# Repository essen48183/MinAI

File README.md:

# MinAI

**A single-file C++ transformer, built to be read.** Every mechanism of a modern LLM — attention, softmax, backprop, residual connections, causal masking — in ~780 lines of heavily commented code. Learns to reverse a list of 8 digits (and sort, shift, or mod-sum), demonstrating in miniature every idea that powers GPT-4.

Descends from Damien Boureille's [ATTN-11](https://github.com/dbrll/ATTN-11) (PDP-11 MACRO-11 assembly) via Dave Plummer's [2.11BSD port](https://github.com/davepl/pdpsrc/tree/main/bsd/attn). Portable C++17 — builds on macOS, Linux, and Windows.

## Why this exists

It's easy to lose the plot on what a large language model does when every explanation starts at "96 transformer blocks". This program is the plot — the irreducible version that still contains every mechanism. If you can read ~780 lines of commented C++, you understand the skeleton of every frontier model. The only difference between this and GPT-4 is quantity: more layers, more heads, more width, more data. Not one new idea.

## Quick start — two paths

### If you just want to run it (no compiler, no programming required)

Prebuilt binaries for common platforms live in [`bin/`](bin/). Grab the one for your platform and run it from a terminal:

| Platform | File | How to run |
|---|---|---|
| **macOS** (Apple Silicon or Intel) | [`bin/macos-universal/minai`](bin/macos-universal/minai) | `./minai` from a terminal |
| **Linux** (x86_64) | [`bin/linux-x86_64/minai`](bin/linux-x86_64/minai) | `./minai` from a terminal |
| **Windows** (x86_64) | [`bin/windows-x86_64/minai.exe`](bin/windows-x86_64/minai.exe) | double-click or run from `cmd`/PowerShell |

See [`bin/README.md`](bin/README.md) for details (including the macOS Gatekeeper first-run workaround). After it runs, `./minai --help` shows every flag.

### If you want to read and modify the source

**macOS / Linux** (any C++17 compiler — clang++ or g++):

```bash
make              # builds ./minai with your default C++ compiler
./minai           # trains the default config and runs a demo
./minai --help    # see all flags
```

**Windows** (and an all-platforms fallback) via CMake:

```bash
cmake -B build
cmake --build build --config Release
./build/minai --help          # macOS/Linux
./build/Release/minai.exe     # Windows MSVC
```

No external dependencies — everything needed is in the standard library. Colored sparkline output uses Unicode block characters; works in macOS Terminal, Linux terminals, and Windows Terminal (the default on Windows 11).

Abridged output:

```
MinAI — fixed example, task=reverse, seq_len=8, batch=1, blocks=1, ffn=on, causal=off
Parameters: 2240    Training steps: 800

step    loss     correct/8
-----   ------   ----------
    1   2.2802   0/8
  ...
  800   0.0078   8/8

Loss curve (800 steps, 60 columns, higher bars = higher loss):
   2.280 |▇▇▇▇▆▆▆▅▅▄▄▃▃▂▂▁▁                                        | 0.008
           step 1                                           step 800

input  : 0 1 2 3 4 5 6 7
output : 7 6 5 4 3 2 1 0
```

## Read the docs

Two companion documents live next to the source. **Read the one that matches you:**

- **[TRAINER.md](TRAINER.md)** / [TRAINER.pdf](TRAINER.pdf) — the terse operator's manual. Flag reference, task zoo, worked examples. If you already know what a transformer is and just want to drive this one, start here.

- **[ARITHMETICOFINTELLIGENCE.md](ARITHMETICOFINTELLIGENCE.md)** / [ARITHMETICOFINTELLIGENCE.pdf](ARITHMETICOFINTELLIGENCE.pdf) — *The Arithmetic of Intelligence*, a three-section textbook that builds every concept from scratch: what a model is, what attention does, why GPUs are suddenly the bottleneck of the AI industry. Section 1 (Chs 1–15) is the simple introduction, grounded in `minai.cpp` and including a hands-on walkthrough of every flag. Section 2 (Chs 16–22) grows the program into `maxai.cpp`, a toy GPT that accepts prompts, tokenizes with BPE, samples with temperature/top-k/top-p, and runs under a KV cache. Section 3 (Chs 23–28) is a career/field essay on where AI is going and why software engineering is not ending. Written for a reader who has taken some math but has never seen *why* any of it mattered; a curious adult with high-school algebra can follow it end to end.

Read either document with `minai.cpp` open alongside. The comments in the source are in the same tone and will not contradict the prose.

## Flags at a glance

```
--blocks=N      stack N transformer layers (1..96, default 1 — 96 matches GPT-3 depth)
--ffn=0|1       include the feed-forward sub-layer (default on)
--causal=0|1    causal attention mask (default off)
--layernorm=0|1 Pre-LN normalization before each sub-layer; makes deep stacks trainable
--random=0|1    train on random sequences + measure held-out accuracy (default off)
--seq_len=N     sequence length 1..32 (attention is O(N^2) in this)
--batch=B       examples averaged per step 1..128 (default 1)
--task=NAME     reverse | sort | shift | mod_sum (default reverse)
--steps=N       training iterations (default 800)
--extra_demos=0|1  run three bonus demos after training (hierarchical weight quantization,
                   speculative decoding, KV cache tiering). Each is a real LLM inference
                   technique, shown in miniature. Adds a few seconds.
```

Try `./minai --random=1 --blocks=2 --batch=16 --layernorm=1 --steps=3000` for a taste of how a real LLM trains in miniature — the model has to generalize, not memorize, and with LN + batch the grokking moment should land well before 3000 steps.

## Repo layout

```
minai.cpp            the program — 19 numbered parts, every line commented
Makefile             one-line clang++ build
TRAINER.md  .pdf     operator's manual
ARITHMETICOFINTELLIGENCE.md .pdf .docx  the book — textbook, toy-GPT growth, career essay
maxai.cpp            the Section-2 companion program (grows from minai.cpp)
README.md            this file
CLAUDE.md            instructions for the AI assistant that maintains this project
md2pdf.sh            regenerates PDFs from the .md sources
LICENSE              MIT
```

## Credit

Damien Boureille wrote the [ATTN-11](https://github.com/dbrll/ATTN-11) original in PDP-11 MACRO-11 assembly. Dave Plummer ported it to 2.11BSD `as`. This repo is the C++/Apple-Silicon rewrite with extensive annotation, a textbook companion, and runtime flags for blocks / FFN / causal / random / seq_len / batch / task. The core idea — "tiny transformer, every mechanism present, no magic" — is entirely theirs.

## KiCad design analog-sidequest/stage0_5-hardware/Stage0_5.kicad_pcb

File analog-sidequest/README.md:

# Analog MinAI — an analog compute side quest

*A parallel project that runs MinAI's math on discrete analog hardware
instead of digital CPUs/GPUs. PCB-fabbable, home-iterable in hours,
and the only reason it is tractable is that MinAI itself is small.*

---

## Why this project exists

Modern AI is a 2017 neural-network architecture running on 1990s-era
graphics hardware, burning megawatts of electricity to simulate physics
that any properly-built analog circuit does for free. Every transistor
in a GPU spends clock cycles computing `a × b + c` with floating-point
arithmetic, when Ohm's law and Kirchhoff's current law will produce the
same answer at the speed of electricity in a resistor grid.

This side project builds a physical demonstration of that argument at a
scale a single engineer can actually fabricate. It uses **MinAI's 2,240
trained weights** as its reference model, because that is a size a
handful of PCBs can hold. A GPT-3-scale analog build would need millions
of tiles and a foundry. A MinAI-scale analog build fits on a desktop.

**The book's small size is the point.** The project does not exist
despite MinAI being tiny; it exists *because* MinAI is tiny. That
smallness is a superpower here — it makes the entire "is this possible
outside a foundry?" question answerable.

---

## What a final working result looks like

A PCIe card that drops into any motherboard. On the card: a host-side
FPGA, a small onboard flash holding trained weights, and an array of
analog matmul tiles. Running MinAI's forward pass on that card should
produce the same tokens the software version produces, using
**picojoules per multiply-accumulate** (versus nanojoules for a digital
GPU) and with **no clocked computation** — the matmul settles at
analog speed.

The card is a proof of concept, not a product. What it proves is:

1. Analog compute really does match the math of a transformer.
2. The energy and speed advantages predicted by physics are measurable
   in hardware, not just simulation.
3. The build is technically within reach of a small team rather than
   an industrial fab.
4. The architecture scales — the same tile miniaturized to silicon
   with RRAM/memristor crosspoints is the known path to million-weight
   single-chip accelerators.

---

## The critical difference from prior attempts

Every commercial analog-AI attempt from 2012–2024 took the same
shortcut: *train the model on NVIDIA, deploy on our analog chip*.
That shortcut has killed every one of them commercially. The
customer math is unavoidable — if the customer already needs a
GPU for training, they just use it for inference too rather than
bring in a second vendor.

**This project treats training on the analog hardware as a
first-class, non-negotiable requirement**, addressed as Stage 0
(in simulation) and Experiment 4 of Stage 1 (on real hardware).

The core framing — different from every prior analog-AI project —
is **noise is the enemy, not representation.** Digital precision
is bounded by the number format (float32 can never exceed its
23-bit mantissa). Analog precision is bounded only by the noise
of the measurement channel, and every noise source (thermal,
flicker, shot, drift, crosstalk, EMI) has a known engineering
countermeasure. Aggressively applying those countermeasures —
precision thin-film components, autozero op-amps, delta-sigma
ADCs, 8-layer stripline PCBs, calibration reference cells — pushes
analog effective precision to **24–28 bits per operation**, which
is *better* than float32 digital on the operations where analog is
naturally exact (Kirchhoff summation, Ohm's-law multiplication,
exp/log/sqrt/tanh through diode and transistor I-V curves).

The architecture combines **three hardware precision amplifiers**
— Q8.8.8 bit-slicing (three analog cells per weight for 24-bit
nominal precision), autozero summing op-amps (20+ bit op-amp
paths), a 32-bit digital gradient accumulator, plus continuous
calibration via dedicated reference cells — with **five software
training tricks** from the 1970s–1990s analog-computing literature
— mixed-precision updates, stochastic rounding, temporal
oversampling, delta encoding, and analog physics as the native
lookup table. Together they clear the precision bar where IBM
research has demonstrated analog training of **96-layer
transformers**, not just shallow networks.

Softmax, sampling, and all nonlinearities stay analog too — the
same physics (diode `exp`, translinear divide, winner-take-all or
ramp-compare samplers) that makes matmul analog-native also makes
these operations analog-native. The host's digital footprint
reduces to: weight-load at boot, prompt-token DAC in, output-token
ID ADC out, and loop control. **One ADC-DAC round-trip per
generated token, not per layer.**

The project refuses to fabricate any hardware until a pure-
software Stage 0 simulator passes **two** gates:

- **Gate 1 (functional):** MaxAI (2 blocks) trains to recognizable
  output at simulated hardware precision.
- **Gate 2 (scaling):** MaxAI scaled to 96 blocks, same per-layer
  precision, also trains to recognizable output — proving the
  architecture scales to GPT depth in principle.

If Gate 1 fails, the project stops. If Gate 2 fails, the
GPT-depth scaling claim is retracted and the project is rescoped
as small-model-only (still valid, but a narrower pitch). Only
passing both gates clears Stage 1 to fabricate hardware.

See `ARCHITECTURE.md` for the five-trick stack and `STAGE0.md` for
the viability gate.

---

## The five stages

Each stage produces a complete, measurable artifact. Each stage's
output is the foundation for the next. Nobody has to commit to
Stage 4 before finishing Stage 1. The project has a clear inflection
at Stage 3: before it, you are proving the hardware *works*; after
it, you are proving it *matters*.

### Stage 0 — the simulator viability gate *(software only, kills the project cheaply if training doesn't work)*

- A C++ simulator of the tile architecture with Q8.8.8 bit-slicing,
  autozero op-amp paths, a 32-bit gradient accumulator,
  calibration reference cells, realistic device noise, write
  quantization, and all nine training tricks implemented.
- Runs the book's MaxAI training loop through the simulator at
  both 2-block depth (Gate 1) and 96-block depth (Gate 2).
- **Pass both gates:** architecture trains at MaxAI scale AND the
  same architecture scales to GPT-depth in principle. Proceed
  to Stage 1 with full scaling claim intact.
- **Pass Gate 1 only:** architecture trains at small scale but
  compound noise kills deeper networks. Project may still
  proceed, but the scaling claim gets retracted and the pitch
  is rescoped to "edge / small-model only."
- **Fail Gate 1:** the architecture does not train at all at this
  precision. Project stops. Zero hardware cost.
- Wall-time estimate: ~two focused weeks. Budget: $0.
- **What Stage 0 buys:** insurance against repeating Mythic's mistake
  of fabricating hardware before knowing if the architecture
  trains, *and* against the Lightmatter mistake of shipping
  hardware whose scaling ceiling wasn't known until silicon was
  in hand.

### Stage 1 — a single Q8.8.8 analog matmul tile *(validation, including one training step on real hardware)*

- Raspberry Pi Zero 2W as host.
- One small PCB holding a 16×16 analog MAC tile (256 weights).
- Performs MinAI's `Q = X @ Wq` projection entirely in analog.
- Host orchestrates: loads weights from microSD, drives inputs, reads
  outputs, compares against a NumPy/C++ reference from the book.
- Budget: **under $100 in parts**, plus your PCB fab.
- Iteration cycle: hours. Swap digipots, rework the nonlinearity, try
  different op-amps, measure on a scope.
- **What Stage 1 buys:** hardware-proven analog matmul, measurable
  against bit-exact software output. Goes no further than "the
  physics is real."

### Stage 2 — a full MinAI block in analog *(architecture proof)*

- Same Pi host, but now ~10 tiles wired together (sharing a
  backplane PCB).
- Holds MinAI's complete weight set (Q, K, V, Wout, W1, W2 of one
  block = ~2,000 weights across roughly 10 tiles).
- Pi does softmax, sampling, EOS, and tile-to-tile coordination.
  Everything else is analog.
- **What Stage 2 buys:** proof that tiling works and that a whole
  transformer block fits. The output still isn't a wow demo — it's
  MinAI still reversing digits — but the multi-tile architecture
  is proven. Everything beyond this is scaling.
- Budget: **a few hundred dollars** in parts.

### Stage 3 — MaxAI in analog *(the raised-eyebrow demo)*

- **The first demo a stranger will care about.** A Raspberry Pi
  driving a larger stack of analog tiles that holds MaxAI's weights
  (~5,000+ parameters, BPE-tokenized character vocabulary).
- User types a prompt. Pi runs the BPE tokenizer, loads token
  embeddings, streams input vectors into the analog tile array.
  Tiles compute matmuls; Pi manages the KV cache and softmax; the
  combined system generates text, token by token, at interactive
  speeds.
- Expected demo: prompt `"four score "` → analog card generates
  `"and seven years ago"`. Shown on a screen next to a laptop
  running the same model in software, producing identical tokens.
- Power budget: roughly a **watt or two** for the entire analog
  stack. The laptop next to it is pulling thirty.
- Budget: **low four figures** in parts, plus a custom backplane PCB.
- **What Stage 3 buys:** a physical artifact that demonstrates
  analog generative AI at a scale anyone can understand. This is
  the demo you show at Hackaday, Supercon, a VC meeting, a research
  group. It answers the question "could this ever matter?"

### Stage 4 — productize *or* miniaturize *(scaling path, pick one or both)*

Two branches, not necessarily exclusive. Stage 4 is the
answer to the "so what comes next?" question after the Stage-3 demo.

**Stage 4a — productize as a PCIe card.**
- Drop the Raspberry Pi. An FPGA on-card becomes the host interface.
- Card exposes a driver interface to the host PC: load weights,
  run inference, return tokens. Looks to the host like any other
  accelerator (TPU, NPU, etc.).
- Physical form: standard PCIe gen 3 ×4 slot card.
- Budget: five figures, six-month design cycle.
- **What Stage 4a buys:** a tangible product — an analog AI card
  someone can buy and plug into their desktop. Market case: edge
  inference for small language models at one-hundredth the power of
  a GPU.

**Stage 4b — miniaturize to silicon.**
- The same tile architecture, shrunk to a CMOS + RRAM process.
- Each digital potentiometer becomes a 1-transistor + 1-memristor
  crosspoint. The op-amps become integrated summing amplifiers.
  Everything else stays.
- A 256×256 tile in 22 nm fits in roughly 0.5 mm². A million-weight
  chip fits on a die smaller than a fingernail.
- Budget: $30k–$100k for a shared MPW run at a foundry that
  supports RRAM (TSMC, SMIC, IMEC).
- **What Stage 4b buys:** the definitive answer to "could this
  scale to GPT?" A single-chip version of MaxAI at a million or
  tens-of-millions of weights, at milliwatts, validates the whole
  architectural thesis. From there, larger tapeouts are engineering
  scaling, not research.

Stages 4a and 4b are not in competition. A small team that reaches
Stage 3 might do 4a first (to generate revenue) and 4b later (once
the architecture is validated enough to spend tapeout money on).

---

## The arc, in one sentence per stage

- **Stage 0:** Prove in software that the architecture can train at all, before any hardware is built.
- **Stage 1:** Prove that analog matmul AND one training step work on real hardware.
- **Stage 2:** Prove the tile architecture scales to a full transformer block, trainable.
- **Stage 3:** Prove the architecture trains and generates real text — the demo that raises eyebrows, with no GPU in the loop after initialization.
- **Stage 4:** Prove the concept scales — either to a consumer-product card or to a silicon die, both carrying training support, not inference-only.

---

## Folder contents

- `README.md` — this file.
- `ARCHITECTURE.md` — the full system architecture, piece by piece,
  with the "normal computer → analog card" mapping spelled out,
  the on-board LayerNorm stage, the stack pattern, the five
  training tricks, and the ranked constraints.
- `STAGE0.md` — **the simulator viability gate. Read first.**
  Software-only. Determines whether hardware is worth building.
- `STAGE1.md` — single-tile validation, now including the training
  experiment. Schematic, parts list, four measurement experiments.
- `STAGE2.md` — full MinAI block across multiple tiles.
- `STAGE3.md` — the MaxAI demo. Text generation from a prompt,
  on an analog-hardware stack that sits next to your laptop.
- `STAGE4.md` — the productize-or-miniaturize fork. PCIe card vs.
  silicon tapeout, both paths laid out, both carrying training
  support (not inference-only).

---

## How this relates to the book

Everything in the *Arithmetic of Intelligence* describes the
mathematics. This side quest asks whether the same mathematics can be
carried out by something other than a stack of floating-point
multipliers in a cloud-hosted GPU. The answer, apparently, is yes —
and small enough to fit on a desk.

If MinAI were larger, this project would be out of reach. It is not.

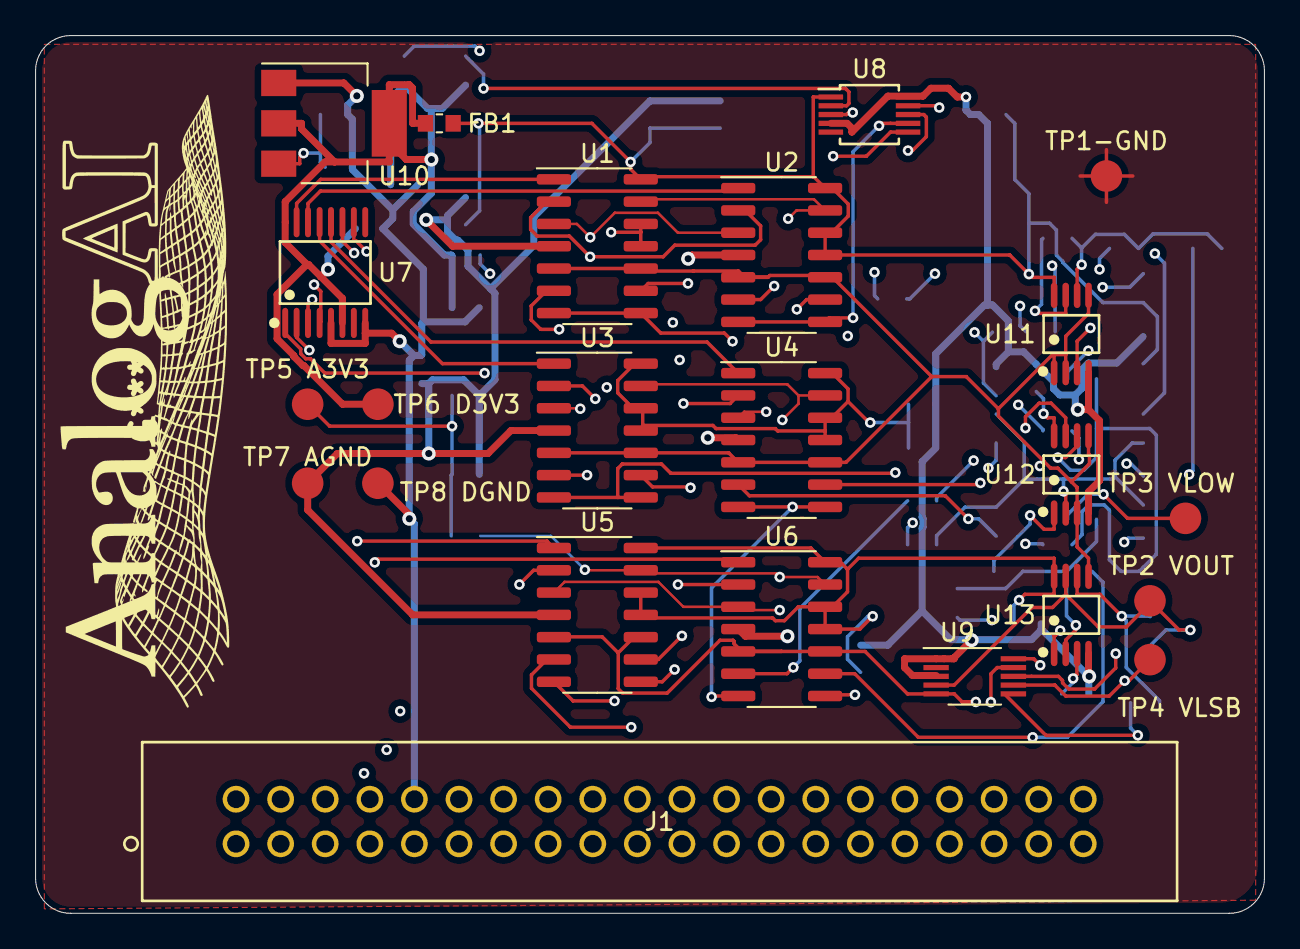
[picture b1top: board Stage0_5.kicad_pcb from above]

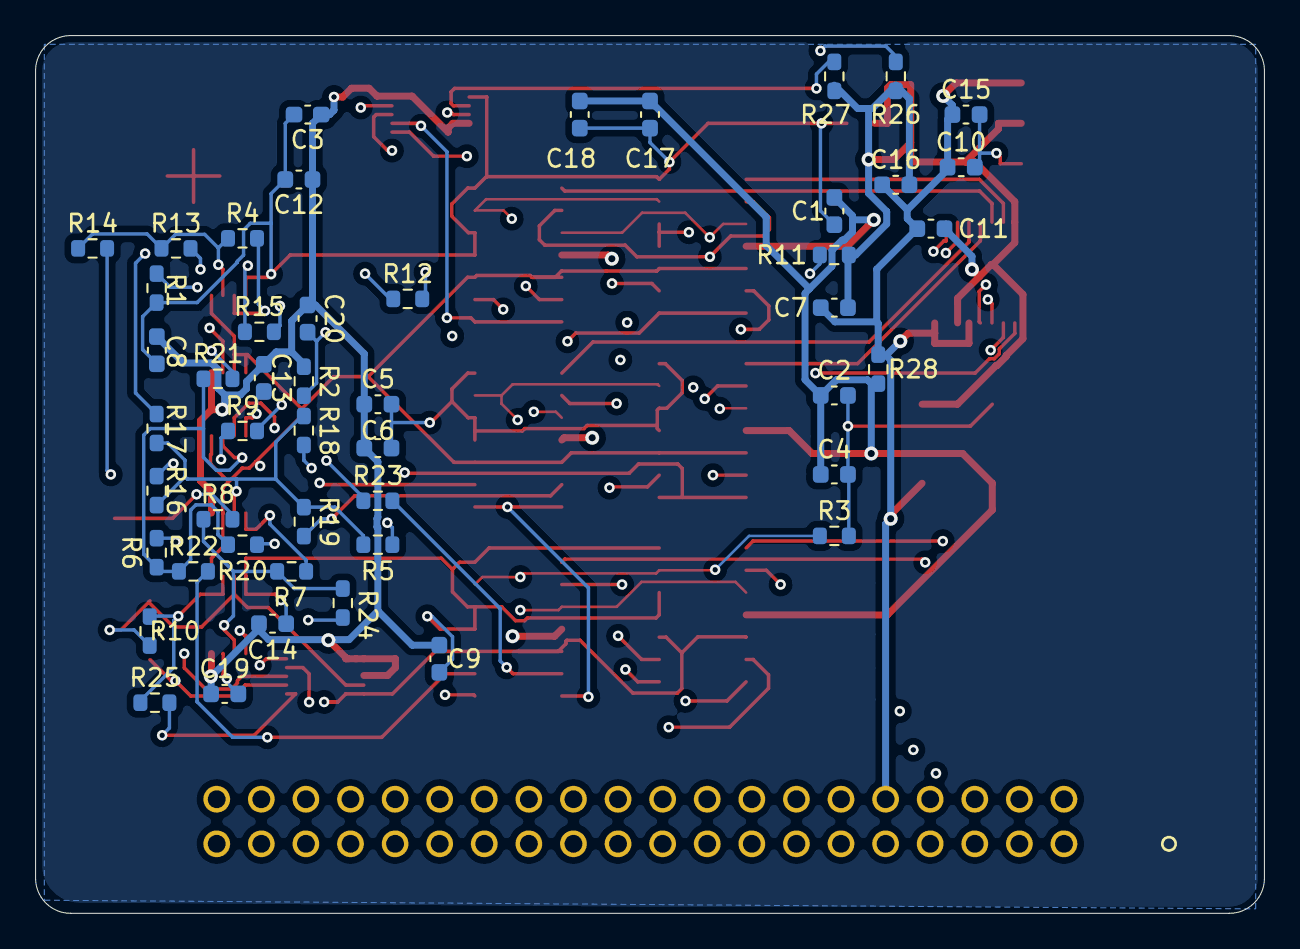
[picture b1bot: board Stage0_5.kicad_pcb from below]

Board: 4 copper layers, 70.0 x 50.0 mm, 71 parts (48 on the bottom side), 48 nets.

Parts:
C1, C2, C3, C4, C5, C6, C7, C8, C9, C10, C11, C12, C13, C14: 100nF; C_0603_1608Metric
C15, C16, C17, C18, C19, C20: 10uF; C_0603_1608Metric
FB1: BLM18AG601SN1D; Fuse_0603_1608Metric
J1: 302-S401
R1, R2, R3, R4, R5, R6, R8, R9, R11: 10k; R_0603_1608Metric
R7, R10: 10k 0.1%; R_0603_1608Metric
R12, R13, R14, R15, R16, R17, R18, R19, R20, R21, R22, R23: 40k 0.1%; R_0603_1608Metric
R24, R25: 2.56M 0.1%; R_0603_1608Metric
R26, R27: 4.7k; R_0603_1608Metric
R28: 13Ω 5%; R_0603_1608Metric
TP1-GND, TP2 VOUT, TP3 VLOW, TP4 VLSB, TP5 A3V3, TP6 D3V3, TP7 AGND, TP8 DGND: Test Point 1.8mm; Test_Point_1.8mm
U1, U2, U3, U4, U5, U6: MCP4251-103E/SL; SOIC-14_3.9x8.7mm_P1.27mm
U7: SN74HC138PWR; easyeda2kicad_TSSOP-16_L5.0-W4.4-P0.65-LS6.4-BL
U8: MCP4728A0T-E/UN; Package_SO_MSOP-10_3x3mm_P0.5mm
U9: ADS1115IDGSR; Package_SO_VSSOP-10_3x3mm_P0.5mm
U10: AMS1117-3.3; Package_TO_SOT_SMD_SOT-223
U11, U12, U13: OPA2333AIDGKTG4; easyeda2kicad_VSSOP-8_L3.0-W3.0-P0.65-LS4.9-BL

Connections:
/5V_PI: C10.1, C15.1, J1.2, J1.4, U10.3 (VIN)
/A3V3: C1.1, C2.1, C3.1, C4.1, C5.1, C6.1, C8.1, C9.1, C12.1, C13.1, C14.1, C17.1, C18.1, FB1.2, R1.1, R3.1, TP5 A3V3.-, U1.11 (~WP), U1.12 (~SHDN), U1.14 (VDD), U2.11 (~WP), U2.12 (~SHDN), U2.14 (VDD), U3.11 (~WP), U3.12 (~SHDN), U3.14 (VDD), U4.11 (~WP), U4.12 (~SHDN), U4.14 (VDD), U5.11 (~WP), U5.12 (~SHDN), U5.14 (VDD), U6.11 (~WP), U6.12 (~SHDN), U6.14 (VDD), U8.1 (VDD), U9.8 (VDD), U11.8 (V+), U12.8 (V+), U13.8 (V+)
/AGND: C1.2, C2.2, C3.2, C4.2, C5.2, C6.2, C8.2, C9.2, C12.2, C13.2, C14.2, C17.2, C18.2, C19.2, C20.2, R2.2, R28.2, TP7 AGND.-, U1.4 (VSS), U2.4 (VSS), U3.4 (VSS), U4.4 (VSS), U5.4 (VSS), U6.4 (VSS), U8.4 (*LDAC), U8.10 (VSS), U9.1 (ADDR), U9.3 (GND), U11.4 (V-), U12.4 (V-), U13.4 (V-)
/CH0_MID_WIPER: R16.1, U1.6 (P1W)
/CH0_MSB_WIPER: R12.1, U1.9 (P0W)
/CH1_MID_WIPER: R17.1, U2.6 (P1W)
/CH1_MSB_WIPER: R13.1, U2.9 (P0W)
/CH2_MID_WIPER: R18.1, U3.6 (P1W)
/CH2_MSB_WIPER: R14.1, U3.9 (P0W)
/CH3_MID_WIPER: R19.1, U4.6 (P1W)
/CH3_MSB_WIPER: R15.1, U4.9 (P0W)
/CS0_N: U1.1 (~CS), U7.15 (Y0)
/CS1_N: U2.1 (~CS), U7.14 (Y1)
/CS2_N: U3.1 (~CS), U7.13 (Y2)
/CS3_N: U4.1 (~CS), U7.12 (Y3)
/CS4_N: U5.1 (~CS), U7.11 (Y4)
/CS5_N: U6.1 (~CS), U7.10 (Y5)
/CS_A0: J1.29, U7.1 (A)
/CS_A1: J1.31, U7.2 (B)
/CS_A2: J1.33, U7.3 (C)
/CS_EN_N: J1.35, R11.2, U7.4 (#G2A)
/D3V3: C7.1, C11.1, C16.1, FB1.1, R11.1, R26.1, R27.1, TP6 D3V3.-, U7.6 (G1), U7.16 (VCC), U10.2 (VOUT), U10.4 (TAB(VOUT))
/DGND: C7.2, C10.2, C11.2, C15.2, C16.2, J1.6, J1.14, J1.20, J1.25, J1.30, J1.34, J1.39, R28.1, TP8 DGND.-, U7.5 (#G2B), U7.8 (GND), U10.1 (GND)
/I2C_SCL: J1.5, R27.2, U8.2 (SCL), U9.10 (SCL)
/I2C_SDA: J1.3, R26.2, U8.3 (SDA), U9.9 (SDA)
/LOW_SUM: R7.2, R8.2, R24.2, U13.2 (-INA)
/LSB0_WIPER: R20.1, U5.9 (P0W)
/LSB1_WIPER: R21.1, U5.6 (P1W)
/LSB2_WIPER: R22.1, U6.9 (P0W)
/LSB3_WIPER: R23.1, U6.6 (P1W)
/LSB_SUM: R6.2, R20.2, R21.2, R22.2, R23.2, U12.6 (-INB)
/MID_SUM: R5.2, R16.2, R17.2, R18.2, R19.2, U12.2 (-INA)
/MSB_SUM: R4.2, R12.2, R13.2, R14.2, R15.2, U11.6 (-INB)
/OUT_SUM: R9.2, R10.2, R25.2, U13.6 (-INB)
/SPI_MISO: J1.21, R3.2, U1.13 (SDO), U2.13 (SDO), U3.13 (SDO), U4.13 (SDO), U5.13 (SDO), U6.13 (SDO)
/SPI_MOSI: J1.19, U1.3 (SDI), U2.3 (SDI), U3.3 (SDI), U4.3 (SDI), U5.3 (SDI), U6.3 (SDI)
/SPI_SCLK: J1.23, U1.2 (SCK), U2.2 (SCK), U3.2 (SCK), U4.2 (SCK), U5.2 (SCK), U6.2 (SCK)
/VCM: C19.1, U1.5 (P1B), U1.10 (P0B), U2.5 (P1B), U2.10 (P0B), U3.5 (P1B), U3.10 (P0B), U4.5 (P1B), U4.10 (P0B), U5.5 (P1B), U5.10 (P0B), U6.5 (P1B), U6.10 (P0B), U9.5 (AIN1), U11.1 (OUTA), U11.2 (-INA), U11.5 (+INB), U12.3 (+INA), U12.5 (+INB), U13.3 (+INA), U13.5 (+INB)
/VCM_DIV: C20.1, R1.2, R2.1, U11.3 (+INA)
/VIN_A: U1.7 (P1A), U1.8 (P0A), U5.8 (P0A), U8.6 (VOUTA)
/VIN_B: U2.7 (P1A), U2.8 (P0A), U5.7 (P1A), U8.7 (VOUTB)
/VIN_C: U3.7 (P1A), U3.8 (P0A), U6.8 (P0A), U8.8 (VOUTC)
/VIN_D: U4.7 (P1A), U4.8 (P0A), U6.7 (P1A), U8.9 (VOUTD)
/V_LOW: R8.1, R25.1, TP3 VLOW.-, U9.6 (AIN2), U13.1 (OUTA)
/V_LSB: R6.1, R24.1, TP4 VLSB.-, U9.7 (AIN3), U12.7 (OUTB)
/V_MID: R5.1, R7.1, U12.1 (OUTA)
/V_MSB: R4.1, R9.1, U11.7 (OUTB)
/V_OUT: R10.1, TP2 VOUT.-, U9.4 (AIN0), U13.7 (OUTB)

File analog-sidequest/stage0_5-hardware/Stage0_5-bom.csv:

Reference,Value,Footprint,Manufacturer Part Number,Manufacturer,Package,Datasheet,Description,LCSC Part Number,DNP,Exclude from BOM
C1,100nF,C_0603_1608Metric,CL10B104KB8NNNC,Samsung Electro-Mechanics,SMD_0603_1608Metric,,Decoupling,,,
C2,100nF,C_0603_1608Metric,CL10B104KB8NNNC,Samsung Electro-Mechanics,SMD_0603_1608Metric,,Decoupling,,,
C3,100nF,C_0603_1608Metric,CL10B104KB8NNNC,Samsung Electro-Mechanics,SMD_0603_1608Metric,,Decoupling,,,
C4,100nF,C_0603_1608Metric,CL10B104KB8NNNC,Samsung Electro-Mechanics,SMD_0603_1608Metric,,Decoupling,,,
C5,100nF,C_0603_1608Metric,CL10B104KB8NNNC,Samsung Electro-Mechanics,SMD_0603_1608Metric,,Decoupling,,,
C6,100nF,C_0603_1608Metric,CL10B104KB8NNNC,Samsung Electro-Mechanics,SMD_0603_1608Metric,,Decoupling,,,
C7,100nF,C_0603_1608Metric,CL10B104KB8NNNC,Samsung Electro-Mechanics,SMD_0603_1608Metric,,Decoupling,,,
C8,100nF,C_0603_1608Metric,CL10B104KB8NNNC,Samsung Electro-Mechanics,SMD_0603_1608Metric,,Decoupling,,,
C9,100nF,C_0603_1608Metric,CL10B104KB8NNNC,Samsung Electro-Mechanics,SMD_0603_1608Metric,,Decoupling,,,
C10,100nF,C_0603_1608Metric,CL10B104KB8NNNC,Samsung Electro-Mechanics,SMD_0603_1608Metric,,Decoupling,,,
C11,100nF,C_0603_1608Metric,CL10B104KB8NNNC,Samsung Electro-Mechanics,SMD_0603_1608Metric,,Decoupling,,,
C12,100nF,C_0603_1608Metric,CL10B104KB8NNNC,Samsung Electro-Mechanics,SMD_0603_1608Metric,,Decoupling,,,
C13,100nF,C_0603_1608Metric,CL10B104KB8NNNC,Samsung Electro-Mechanics,SMD_0603_1608Metric,,Decoupling,,,
C14,100nF,C_0603_1608Metric,CL10B104KB8NNNC,Samsung Electro-Mechanics,SMD_0603_1608Metric,,Decoupling,,,
C15,10uF,C_0603_1608Metric,C2012X5R1A106M085AB,TDK,SMD_0805_2012Metric,,Bulk,,,
C16,10uF,C_0603_1608Metric,C2012X5R1A106M085AB,TDK,SMD_0805_2012Metric,,Bulk,,,
C17,10uF,C_0603_1608Metric,C2012X5R1A106M085AB,TDK,SMD_0805_2012Metric,,Bulk,,,
C18,10uF,C_0603_1608Metric,C2012X5R1A106M085AB,TDK,SMD_0805_2012Metric,,Bulk,,,
C19,10uF,C_0603_1608Metric,C2012X5R1A106M085AB,TDK,SMD_0805_2012Metric,,Bulk,,,
C20,10uF,C_0603_1608Metric,C2012X5R1A106M085AB,TDK,SMD_0805_2012Metric,,Bulk,,,
FB1,BLM18AG601SN1D,Fuse:0603_1608Metric,BLM18AG601SN1D,Murata Electronics,0603,https://www.murata.com/en-us/products/productdata/8796738650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,Rail Filter,,,
J1,302-S401,302-S401,302-S401,On Shore Technology Inc.,2x20 TH 2.54mm,https://mm.digikey.com/Volume0/opasdata/d220001/medias/docus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,Host Interface Header,,,
R1,10k,R_0603_1608Metric,RC0603FR-1310KL,Yageo,SMD_0603_1608Metric,,Bias and Feedback,,,
R2,10k,R_0603_1608Metric,RC0603FR-1310KL,Yageo,SMD_0603_1608Metric,,Bias and Feedback,,,
R3,10k,R_0603_1608Metric,RC0603FR-1310KL,Yageo,SMD_0603_1608Metric,,Bias and Feedback,,,
R4,10k,R_0603_1608Metric,RC0603FR-1310KL,Yageo,SMD_0603_1608Metric,,Bias and Feedback,,,
R5,10k,R_0603_1608Metric,RC0603FR-1310KL,Yageo,SMD_0603_1608Metric,,Bias and Feedback,,,
R6,10k,R_0603_1608Metric,RC0603FR-1310KL,Yageo,SMD_0603_1608Metric,,Bias and Feedback,,,
R7,10k,R_0603_1608Metric,RC0603FR-1310KL,Yageo,SMD_0603_1608Metric,,Bias and Feedback,,,
R8,10k,R_0603_1608Metric,RC0603FR-1310KL,Yageo,SMD_0603_1608Metric,,Bias and Feedback,,,
R9,10k,R_0603_1608Metric,RC0603FR-1310KL,Yageo,SMD_0603_1608Metric,,Bias and Feedback,,,
R10,10k,R_0603_1608Metric,RC0603FR-1310KL,Yageo,SMD_0603_1608Metric,,Bias and Feedback,,,
R11,10k,R_0603_1608Metric,RC0603FR-1310KL,Yageo,SMD_0603_1608Metric,,Bias and Feedback,,,
R12,40k 0.1%,R_0603_1608Metric,PAT0603E4002BST1,Vishay Dale Thin Film,SMD_0603_1608Metric,,Slice Summing Input,,,
R13,40k 0.1%,R_0603_1608Metric,PAT0603E4002BST1,Vishay Dale Thin Film,SMD_0603_1608Metric,,Slice Summing Input,,,
R14,40k 0.1%,R_0603_1608Metric,PAT0603E4002BST1,Vishay Dale Thin Film,SMD_0603_1608Metric,,Slice Summing Input,,,
R15,40k 0.1%,R_0603_1608Metric,PAT0603E4002BST1,Vishay Dale Thin Film,SMD_0603_1608Metric,,Slice Summing Input,,,
R16,40k 0.1%,R_0603_1608Metric,PAT0603E4002BST1,Vishay Dale Thin Film,SMD_0603_1608Metric,,Slice Summing Input,,,
R17,40k 0.1%,R_0603_1608Metric,PAT0603E4002BST1,Vishay Dale Thin Film,SMD_0603_1608Metric,,Slice Summing Input,,,
R18,40k 0.1%,R_0603_1608Metric,PAT0603E4002BST1,Vishay Dale Thin Film,SMD_0603_1608Metric,,Slice Summing Input,,,
R19,40k 0.1%,R_0603_1608Metric,PAT0603E4002BST1,Vishay Dale Thin Film,SMD_0603_1608Metric,,Slice Summing Input,,,
R20,40k 0.1%,R_0603_1608Metric,PAT0603E4002BST1,Vishay Dale Thin Film,SMD_0603_1608Metric,,Slice Summing Input,,,
R21,40k 0.1%,R_0603_1608Metric,PAT0603E4002BST1,Vishay Dale Thin Film,SMD_0603_1608Metric,,Slice Summing Input,,,
R22,40k 0.1%,R_0603_1608Metric,PAT0603E4002BST1,Vishay Dale Thin Film,SMD_0603_1608Metric,,Slice Summing Input,,,
R23,40k 0.1%,R_0603_1608Metric,PAT0603E4002BST1,Vishay Dale Thin Film,SMD_0603_1608Metric,,Slice Summing Input,,,
R24,2.56M 0.1%,R_0603_1608Metric,PAT0603E2564BST1,Vishay Dale Thin Film,SMD_0603_1608Metric,,Binary Scaling,,,
R25,2.56M 0.1%,R_0603_1608Metric,PAT0603E2564BST1,Vishay Dale Thin Film,SMD_0603_1608Metric,,Binary Scaling,,,
R26,4.7k,R_0603_1608Metric,RC0603FR-074K7L,Yageo,SMD_0603_1608Metric,,Pull-Up,,,
R27,4.7k,R_0603_1608Metric,RC0603FR-074K7L,Yageo,SMD_0603_1608Metric,,Pull-Up,,,
R28,0,R_0603_1608Metric,RC0603JR-130RL,Yageo,SMD_0603_1608Metric,,Star Ground Tie,,,
U1,MCP4251-103E/SL,SOIC-14_3.9x8.7mm_P1.27mm,MCP4251-103E/SL,Microchip,SOIC-14,https://ww1.microchip.com/downloads/en/DeviceDoc/22060b.pdf,Programmable Weight Slice,,,
U2,MCP4251-103E/SL,SOIC-14_3.9x8.7mm_P1.27mm,MCP4251-103E/SL,Microchip,SOIC-14,https://ww1.microchip.com/downloads/en/DeviceDoc/22060b.pdf,Programmable Weight Slice,,,
U3,MCP4251-103E/SL,SOIC-14_3.9x8.7mm_P1.27mm,MCP4251-103E/SL,Microchip,SOIC-14,https://ww1.microchip.com/downloads/en/DeviceDoc/22060b.pdf,Programmable Weight Slice,,,
U4,MCP4251-103E/SL,SOIC-14_3.9x8.7mm_P1.27mm,MCP4251-103E/SL,Microchip,SOIC-14,https://ww1.microchip.com/downloads/en/DeviceDoc/22060b.pdf,Programmable Weight Slice,,,
U5,MCP4251-103E/SL,SOIC-14_3.9x8.7mm_P1.27mm,MCP4251-103E/SL,Microchip,SOIC-14,https://ww1.microchip.com/downloads/en/DeviceDoc/22060b.pdf,Programmable Weight Slice,,,
U6,MCP4251-103E/SL,SOIC-14_3.9x8.7mm_P1.27mm,MCP4251-103E/SL,Microchip,SOIC-14,https://ww1.microchip.com/downloads/en/DeviceDoc/22060b.pdf,Programmable Weight Slice,,,
U7,SN74HC138PWR,easyeda2kicad:TSSOP-16_L5.0-W4.4-P0.65-LS6.4-BL,SN74HC138PWR,TI(德州仪器),TSSOP-16,https://storage.googleapis.com/graviton-electric-symbols/doc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,Chip-Select Decoder,C157527,,
U8,MCP4728A0T-E/UN,Package_SO:MSOP-10_3x3mm_P0.5mm,MCP4728A0T-E/UN,Microchip Technology,MSOP-10,https://ww1.microchip.com/downloads/en/DeviceDoc/22187E.pdf,Input DAC,,,
U9,ADS1115IDGSR,Package_SO:VSSOP-10_3x3mm_P0.5mm,ADS1115IDGSR,Texas Instruments,VSSOP-10,https://www.ti.com/general/docs/suppproductinfo.tsp?distId=1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,Output ADC,,,
U10,AMS1117-3.3,Package_TO_SOT_SMD:SOT-223,AMS1117-3.3,AMS ,SOT-223,http://www.advanced-monolithic.com/pdf/ds1117.pdf,3.3V Regulator,,,
U11,OPA2333AIDGKTG4,easyeda2kicad:VSSOP-8_L3.0-W3.0-P0.65-LS4.9-BL,OPA2333AIDGKTG4,TI(德州仪器),VSSOP-8,,Precision Summing Amplifier,C2060187,,
U12,OPA2333AIDGKTG4,easyeda2kicad:VSSOP-8_L3.0-W3.0-P0.65-LS4.9-BL,OPA2333AIDGKTG4,TI(德州仪器),VSSOP-8,,Precision Summing Amplifier,C2060187,,
U13,OPA2333AIDGKTG4,easyeda2kicad:VSSOP-8_L3.0-W3.0-P0.65-LS4.9-BL,OPA2333AIDGKTG4,TI(德州仪器),VSSOP-8,,Precision Summing Amplifier,C2060187,,

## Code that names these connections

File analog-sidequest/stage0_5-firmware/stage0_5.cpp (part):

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    printf("=============================================================\n");

    const char* slice_names[3] = { "MSB", "middle", "LSB" };
    const int   adc_channels[3] = { 1, 2, 3 };  // V_msb, V_mid, V_lsb

    bool all_pass = true;

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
